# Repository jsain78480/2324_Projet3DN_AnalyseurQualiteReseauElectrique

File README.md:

# 2324_Projet3DN_AnalyseurQualiteReseauElectrique

# Consignes du projet
Il nous a été demandé de réaliser un projet de troisième année d'ingénieur en utilisant un STM32.
Le sujet de projet doit être validé avec le corps enseignant et doit être assez volumineux (Etaler sur 62h en autonomie).
Un GITHUB doit être créé et doit intégrer l'ensemble des éléments pour la création du projet (planning, cahier des charges, etc).
Il est préférable de réaliser un PCB 4 couches et de sous-traiter sa fabrication.
Les composants devront être soudé par les élèves. 

## Organisation du GITHUB

Nous avons ajouté différentes catégories dans notre GITHUB :
1) Hardware intègre tous les éléments permettant d'aboutir à la fabrication de nos PCB :       
   https://github.com/jsain78480/2324_Projet3DN_AnalyseurQualiteReseauElectrique/tree/main/Hardware 
2) Software intègre toute la programmation logiciel liée à STM32 Cube IDE :
   https://github.com/jsain78480/2324_Projet3DN_AnalyseurQualiteReseauElectrique/tree/main/Software
3) Projet intègre toute la méthodologie projet (Planning, cahier des charges) :
   https://github.com/jsain78480/2324_Projet3DN_AnalyseurQualiteReseauElectrique/tree/main/Projet

## Résumé du projet
Nous souhaitons réaliser un analyseur de réseau électrique dans le but d'évaluer la qualité d'un réseau electrique d'une entreprise.
Cette analyse permettra également à l'entreprise d'évaluer sa consommation électrique globale et de réévaluer l'offre qu'elle souscrit auprès de leur fournisseur.
Ce dispositif permet :
  - De récupérer la tension électrique du réseau monophasée ou triphasée
  - De mesurer le courant
  - De prélever la puissance du réseau
  - De prélever le spectre et en ressortir les harmoniques
  - D'afficher sur un écran les mesures instantannées
  - Gérer des alertes si le réseau comporte des problèmes

Le projet a commencé le 26 février et s'étend sur 62h. 
Vous pouvez trouver le planing du projet dans le répertoire projet.

## Le schéma du projet

## Le PCB d'acquisition

## Le PCB de traitement

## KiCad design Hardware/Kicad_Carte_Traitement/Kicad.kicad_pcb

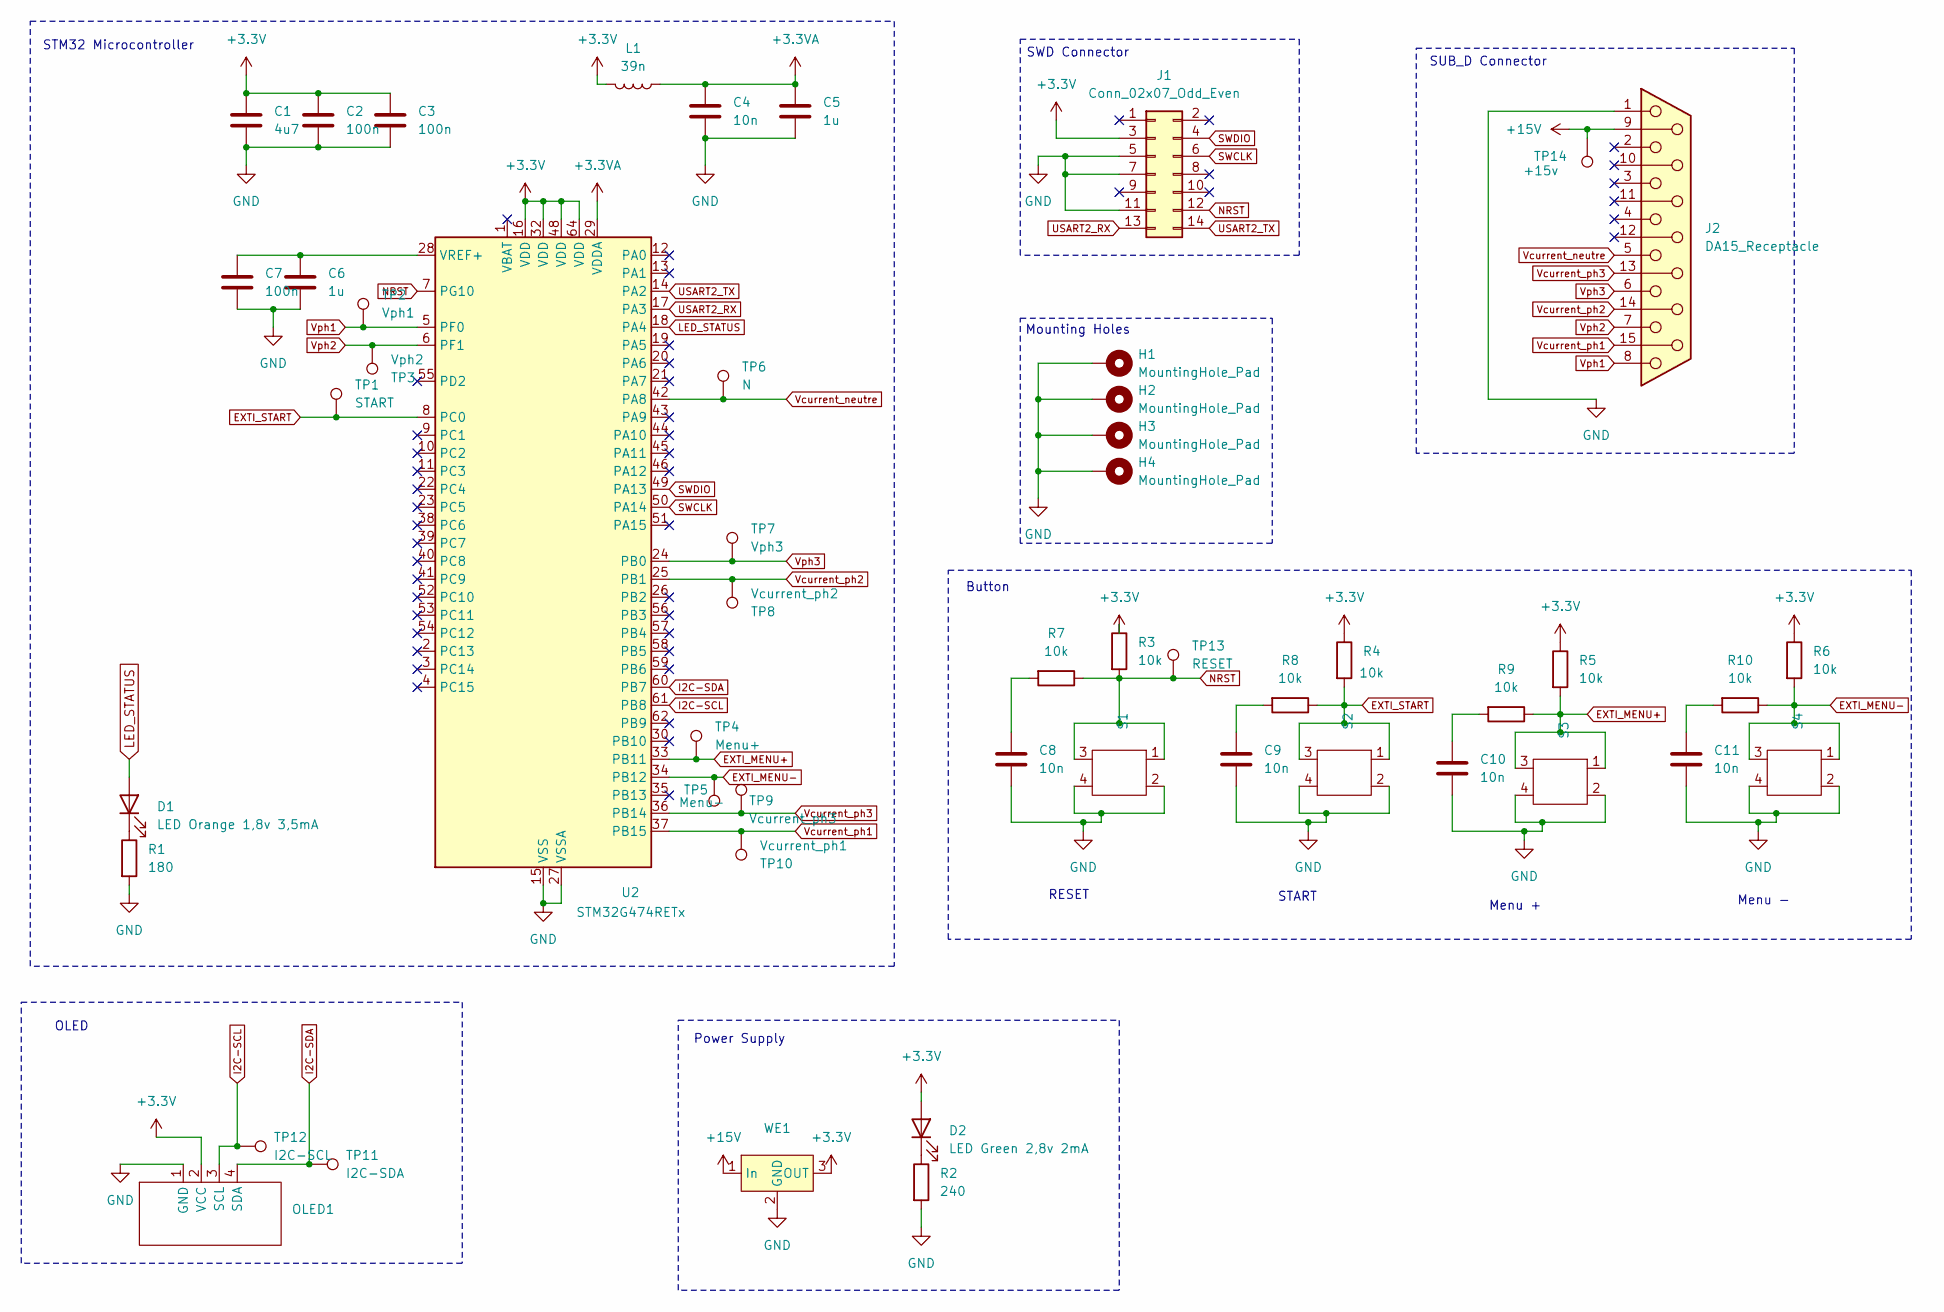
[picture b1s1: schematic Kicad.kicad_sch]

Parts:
C1: 4u7; C_0603_1608Metric_Pad1.08x0.95mm_HandSolder
C2, C3, C7: 100n; C_0603_1608Metric_Pad1.08x0.95mm_HandSolder
C4, C8, C9, C10, C11: 10n; C_0603_1608Metric_Pad1.08x0.95mm_HandSolder
C5, C6: 1u; C_0603_1608Metric_Pad1.08x0.95mm_HandSolder
D1: LED Orange 1,8v 3,5mA; LED_0603_1608Metric_Pad1.05x0.95mm_HandSolder
D2: LED Green 2,8v 2mA; LED_0603_1608Metric_Pad1.05x0.95mm_HandSolder
H1, H2, H3, H4: MountingHole_Pad; MountingHole_3.2mm_M3_Pad
J1: Conn_02x07_Odd_Even; IDC-Header_2x07_P2.54mm_Vertical_SMD
J2: DA15_Receptacle; 618015231321
L1: 39n; L_0603_1608Metric_Pad1.05x0.95mm_HandSolder
OLED1: OLED
R1: 180; R_0603_1608Metric_Pad0.98x0.95mm_HandSolder
R2: 240; R_0603_1608Metric_Pad0.98x0.95mm_HandSolder
R3, R4, R5, R6, R7, R8, R9, R10: 10k; R_0603_1608Metric_Pad0.98x0.95mm_HandSolder
S1, S2, S3, S4: Tact_switch
TP1: START; Pin_D1.2mm_L10.2mm_W2.9mm_FlatFork
TP2: Vph1; Pin_D1.2mm_L10.2mm_W2.9mm_FlatFork
TP3: Vph2; Pin_D1.2mm_L10.2mm_W2.9mm_FlatFork
TP4: Menu+; Pin_D1.2mm_L10.2mm_W2.9mm_FlatFork
TP5: Menu-; Pin_D1.2mm_L10.2mm_W2.9mm_FlatFork
TP6: N; Pin_D1.2mm_L10.2mm_W2.9mm_FlatFork
TP7: Vph3; Pin_D1.2mm_L10.2mm_W2.9mm_FlatFork
TP8: Vcurrent_ph2; Pin_D1.2mm_L10.2mm_W2.9mm_FlatFork
TP9: Vcurrent_ph3; Pin_D1.2mm_L10.2mm_W2.9mm_FlatFork
TP10: Vcurrent_ph1; Pin_D1.2mm_L10.2mm_W2.9mm_FlatFork
TP11: I2C-SDA; Pin_D1.2mm_L10.2mm_W2.9mm_FlatFork
TP12: I2C-SCL; Pin_D1.2mm_L10.2mm_W2.9mm_FlatFork
TP13: RESET; Pin_D1.2mm_L10.2mm_W2.9mm_FlatFork
TP14: +15v; Pin_D1.2mm_L10.2mm_W2.9mm_FlatFork
U2: STM32G474RETx; LQFP-64_10x10mm_P0.5mm
WE1: test

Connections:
+3.3V: C1.1, C2.1, C3.1, D2.2 (A), J1.3, L1.2, OLED1.2 (VCC), R3.1, R4.1, R5.1, R6.1, U2.16 (VDD), U2.32 (VDD), U2.48 (VDD), U2.64 (VDD), WE1.3 (OUT)
+3.3VA: C4.1, C5.1, L1.1, U2.29 (VDDA)
+15V: J2.9, TP14.1, WE1.1 (In)
EXTI_MENU+: R5.2, R9.1, S3.1, S3.3, TP4.1, U2.33 (PB11)
EXTI_MENU-: R6.2, R10.1, S4.1, S4.3, TP5.1, U2.34 (PB12)
EXTI_START: R4.2, R8.1, S2.1, S2.3, TP1.1, U2.8 (PC0)
GND: C1.2, C2.2, C3.2, C4.2, C5.2, C6.2, C7.2, C8.2, C9.2, C10.2, C11.2, H1.1, H2.1, H3.1, H4.1, J1.5, J1.7, J1.11, J2.1, OLED1.1 (GND), R1.2, R2.2, S1.2, S1.4, S2.2, S2.4, S3.2, S3.4, S4.2, S4.4, U2.15 (VSS), U2.27 (VSSA), U2.31 (VSS), U2.47 (VSS), U2.63 (VSS), WE1.2 (GND)
I2C-SCL: OLED1.3 (SCL), TP12.1, U2.61 (PB8)
I2C-SDA: OLED1.4 (SDA), TP11.1, U2.60 (PB7)
LED_STATUS: D1.2 (A), U2.18 (PA4)
NRST: J1.12, R3.2, R7.1, S1.1, S1.3, TP13.1, U2.7 (PG10)
unnamed: C8.1, R7.2
unnamed: C9.1, R8.2
unnamed: C10.1, R9.2
unnamed: C11.1, R10.2
unnamed: D1.1 (K), R1.1
unnamed: D2.1 (K), R2.1
unnamed: C6.1, C7.1, U2.28 (VREF+)
SWCLK: J1.6, U2.50 (PA14)
SWDIO: J1.4, U2.49 (PA13)
USART2_RX: J1.13, U2.17 (PA3)
USART2_TX: J1.14, U2.14 (PA2)
Vcurrent_neutre: J2.5, TP6.1, U2.42 (PA8)
Vcurrent_ph1: J2.15, TP10.1, U2.37 (PB15)
Vcurrent_ph2: J2.14, TP8.1, U2.25 (PB1)
Vcurrent_ph3: J2.13, TP9.1, U2.36 (PB14)
Vph1: J2.8, TP2.1, U2.5 (PF0)
Vph2: J2.7, TP3.1, U2.6 (PF1)
Vph3: J2.6, TP7.1, U2.24 (PB0)

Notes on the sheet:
STM32 Microcontroller
Power Supply
SUB_D Connector
Menu -
Button
SWD Connector
OLED
START
RESET
Menu +
Mounting Holes

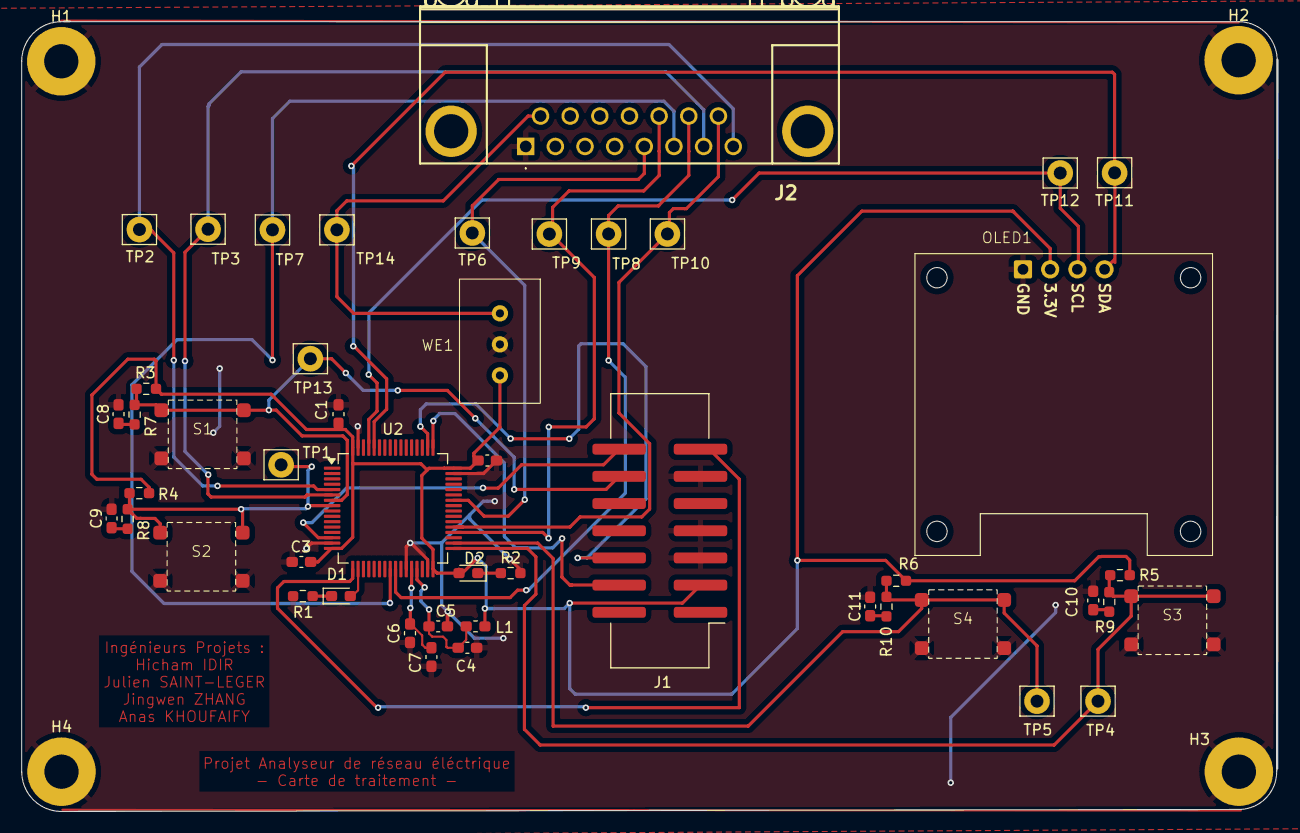
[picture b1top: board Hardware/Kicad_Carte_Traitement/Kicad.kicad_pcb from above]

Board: 2 copper layers, 117.3 x 73.8 mm, 51 parts (0 on the bottom side), 29 nets.

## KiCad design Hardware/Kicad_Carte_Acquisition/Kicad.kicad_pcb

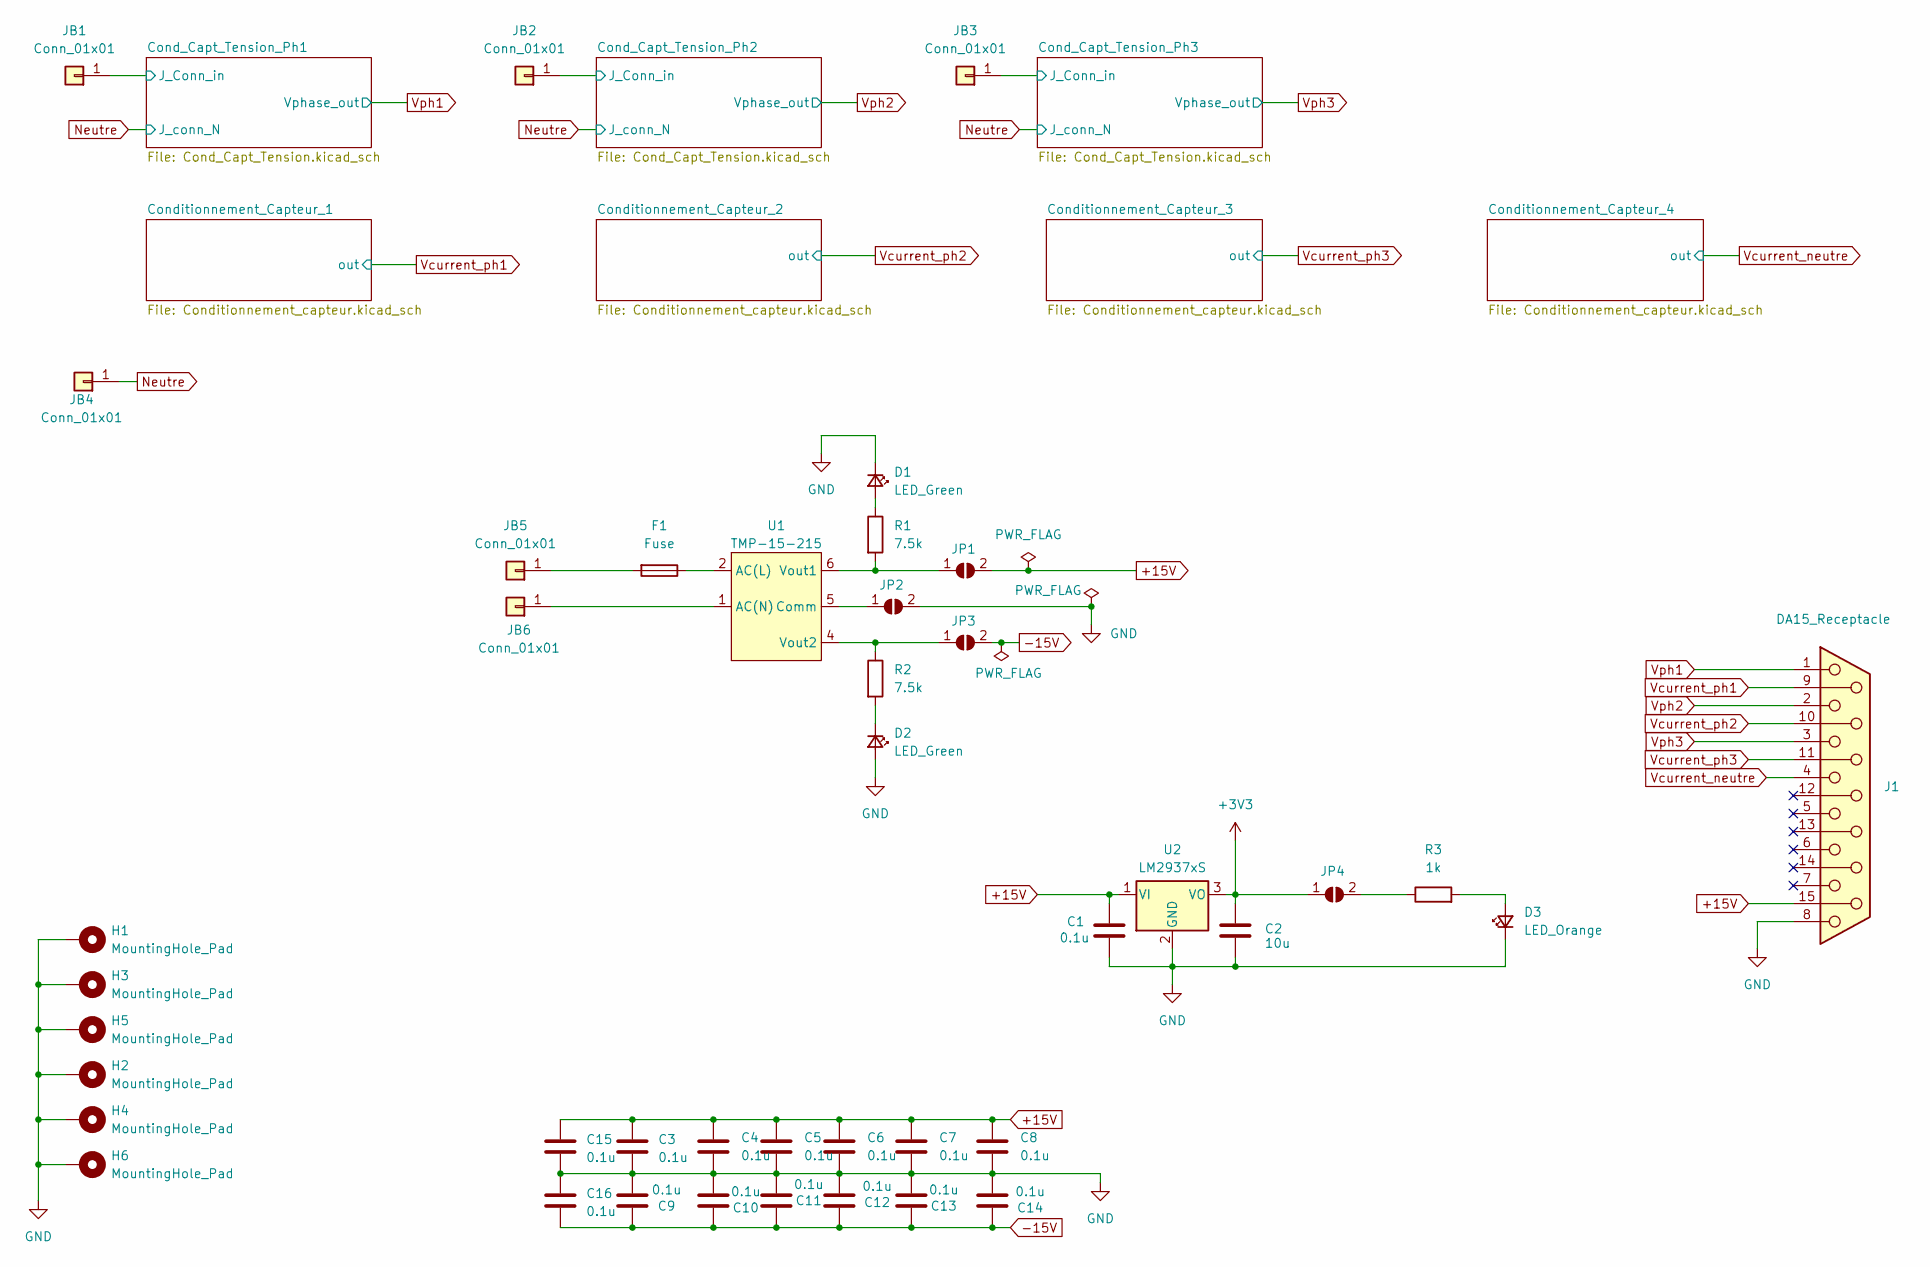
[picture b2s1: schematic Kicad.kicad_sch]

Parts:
C1, C3, C4, C5, C6, C7, C8, C9, C10, C11, C12, C13, C14, C15, C16: 0.1u; C_0603_1608Metric_Pad1.08x0.95mm_HandSolder
C2: 10u; C_0603_1608Metric_Pad1.08x0.95mm_HandSolder
D1, D2: LED_Green; LED_0603_1608Metric_Pad1.05x0.95mm_HandSolder
D3: LED_Orange; LED_0603_1608Metric_Pad1.05x0.95mm_HandSolder
F1: Fuse; Porte_Fusible_PC1E
H1, H2, H3, H4, H5, H6: MountingHole_Pad; MountingHole_3.2mm_M3_Pad
J1: DA15_Receptacle; 618015231321
JB1, JB2, JB3, JB4, JB5, JB6: Conn_01x01; Banana_Cliff_FCR7350B_S16N-PC_Horizontal
JP1, JP2, JP3, JP4: SolderJumper_2_Open; SolderJumper-2_P1.3mm_Open_TrianglePad1.0x1.5mm
R1, R2: 7.5k; R_0603_1608Metric_Pad0.98x0.95mm_HandSolder
R3: 1k; R_0603_1608Metric_Pad0.98x0.95mm_HandSolder
U1: TMP-15-215; TMP-15-215E
U2: LM2937xS; TO-263-3_TabPin2

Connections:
+3V3: C2.1, JP4.1 (A), U2.3 (VO); also elsewhere on the board
+15V: C1.1, C3.1, C4.1, C5.1, C6.1, C7.1, C8.1, C15.1, J1.15, JP1.2 (B), U2.1 (VI); also elsewhere on the board
-15V: C9.1, C10.1, C11.1, C12.1, C13.1, C14.1, C16.2, JP3.2 (B); also elsewhere on the board
/Cond_Capt_Tension_Ph1/J_Conn_in: JB1.1; also elsewhere on the board
/Cond_Capt_Tension_Ph2/J_Conn_in: JB2.1; also elsewhere on the board
/Cond_Capt_Tension_Ph3/J_Conn_in: JB3.1; also elsewhere on the board
GND: C1.2, C2.2, C3.2, C4.2, C5.2, C6.2, C7.2, C8.2, C9.2, C10.2, C11.2, C12.2, C13.2, C14.2, C15.2, C16.1, D1.1 (K), D2.2 (A), D3.1 (K), H1.1, H2.1, H3.1, H4.1, H5.1, H6.1, J1.8, JP2.2 (B), U2.2 (GND); also elsewhere on the board
unnamed: D1.2 (A), R1.1
unnamed: D2.1 (K), R2.2
unnamed: D3.2 (A), R3.2
unnamed: F1.2, JB5.1
unnamed: JB6.1, U1.1 (AC(N))
unnamed: JP1.1 (A), R1.2, U1.6 (Vout1)
unnamed: JP2.1 (A), U1.5 (Comm)
unnamed: JP3.1 (A), R2.1, U1.4 (Vout2)
unnamed: JP4.2 (B), R3.1
unnamed: F1.1, U1.2 (AC(L))
Neutre: JB4.1; also elsewhere on the board
Vcurrent_neutre: J1.4; also elsewhere on the board
Vcurrent_ph1: J1.9; also elsewhere on the board
Vcurrent_ph2: J1.10; also elsewhere on the board
Vcurrent_ph3: J1.11 (P111); also elsewhere on the board
Vph1: J1.1; also elsewhere on the board
Vph2: J1.2; also elsewhere on the board
Vph3: J1.3; also elsewhere on the board

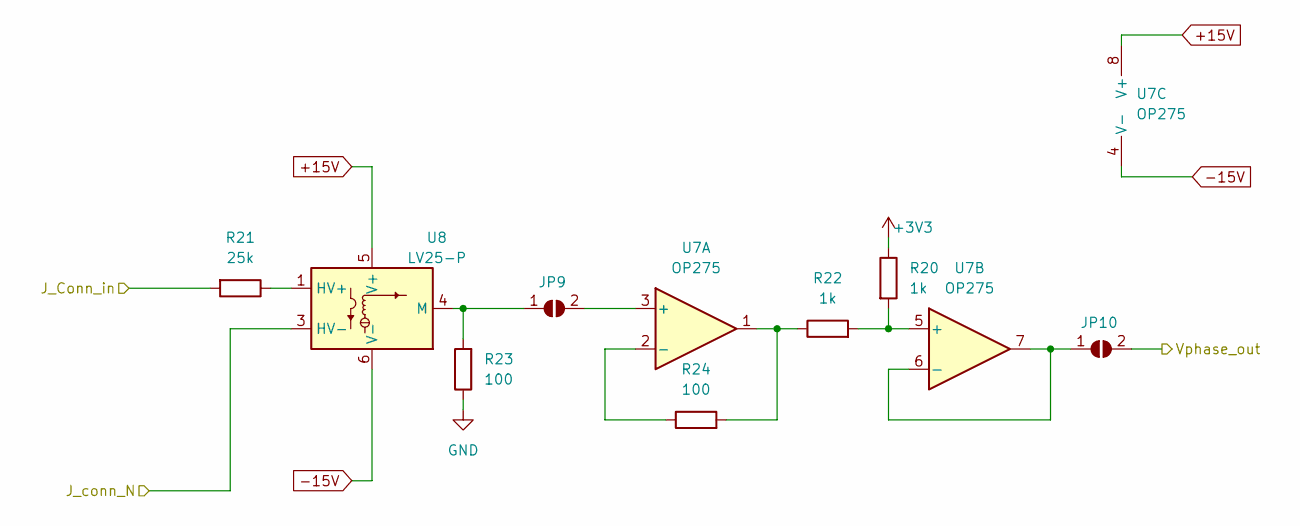
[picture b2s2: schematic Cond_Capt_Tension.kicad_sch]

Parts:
JP9, JP10: SolderJumper_2_Open; SolderJumper-2_P1.3mm_Open_TrianglePad1.0x1.5mm
R20, R22: 1k; R_0603_1608Metric_Pad0.98x0.95mm_HandSolder
R21: 25k; R_4527_M11470E
R23, R24: 100; R_0603_1608Metric_Pad0.98x0.95mm_HandSolder
U7: OP275; SOIC-8_3.9x4.9mm_P1.27mm
U8: LV25-P; LEM_LV25-P

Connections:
+3V3: R20.1; also elsewhere on the board
+15V: U7.8 (V+), U8.5 (V+); also elsewhere on the board
-15V: U7.4 (V-), U8.6 (V-); also elsewhere on the board
/Cond_Capt_Tension_Ph1/J_Conn_in: R21.2; also elsewhere on the board
GND: R23.1; also elsewhere on the board
unnamed: JP9.1 (A), R23.2, U8.4 (M)
unnamed: JP9.2 (B), U7.3 (+)
unnamed: JP10.1 (A), U7.6 (-), U7.7
unnamed: R22.1, R24.2, U7.1
unnamed: R24.1, U7.2 (-)
unnamed: R20.2, R22.2, U7.5 (+)
unnamed: R21.1, U8.1 (HV+)
Neutre: U8.3 (HV-); also elsewhere on the board
Vph1: JP10.2 (B); also elsewhere on the board

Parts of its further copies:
JP11, JP12, JP13, JP14: SolderJumper_2_Open; SolderJumper-2_P1.3mm_Open_TrianglePad1.0x1.5mm
R25, R27, R30, R32: 1k; R_0603_1608Metric_Pad0.98x0.95mm_HandSolder
R26, R31: 25k; R_4527_M11470E
R28, R29, R33, R34: 100; R_0603_1608Metric_Pad0.98x0.95mm_HandSolder
U9, U11: OP275; SOIC-8_3.9x4.9mm_P1.27mm
U10, U12: LV25-P; LEM_LV25-P

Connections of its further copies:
+3V3: R25.1, R30.1; also elsewhere on the board
+15V: U9.8 (V+), U10.5 (V+), U11.8 (V+), U12.5 (V+); also elsewhere on the board
-15V: U9.4 (V-), U10.6 (V-), U11.4 (V-), U12.6 (V-); also elsewhere on the board
/Cond_Capt_Tension_Ph2/J_Conn_in: R26.2; also elsewhere on the board
/Cond_Capt_Tension_Ph3/J_Conn_in: R31.2; also elsewhere on the board
GND: R28.1, R33.1; also elsewhere on the board
unnamed: JP11.1 (A), R28.2, U10.4 (M)
unnamed: JP11.2 (B), U9.3 (+)
unnamed: JP12.1 (A), U9.6 (-), U9.7
unnamed: JP13.1 (A), R33.2, U12.4 (M)
unnamed: JP13.2 (B), U11.3 (+)
unnamed: JP14.1 (A), U11.6 (-), U11.7
unnamed: R27.1, R29.2, U9.1
unnamed: R32.1, R34.2, U11.1
unnamed: R29.1, U9.2 (-)
unnamed: R25.2, R27.2, U9.5 (+)
unnamed: R26.1, U10.1 (HV+)
unnamed: R34.1, U11.2 (-)
unnamed: R30.2, R32.2, U11.5 (+)
unnamed: R31.1, U12.1 (HV+)
Neutre: U10.3 (HV-), U12.3 (HV-); also elsewhere on the board
Vph2: JP12.2 (B); also elsewhere on the board
Vph3: JP14.2 (B); also elsewhere on the board

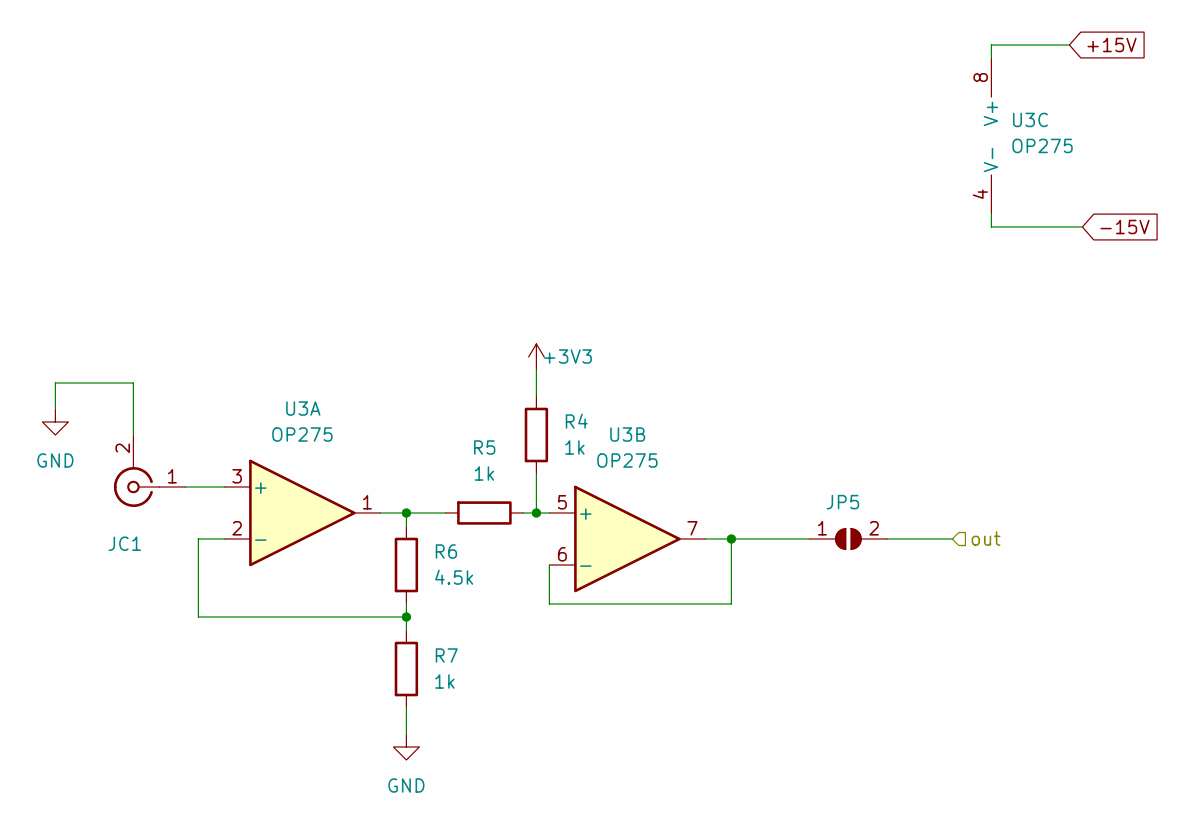
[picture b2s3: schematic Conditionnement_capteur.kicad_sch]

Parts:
JC1: Conn_Coaxial; Conn_CoaxE
JP5: SolderJumper_2_Open; SolderJumper-2_P1.3mm_Open_TrianglePad1.0x1.5mm
R4, R5, R7: 1k; R_0603_1608Metric_Pad0.98x0.95mm_HandSolder
R6: 4.5k; R_0603_1608Metric_Pad0.98x0.95mm_HandSolder
U3: OP275; SOIC-8_3.9x4.9mm_P1.27mm

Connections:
+3V3: R4.1; also elsewhere on the board
+15V: U3.8 (V+); also elsewhere on the board
-15V: U3.4 (V-); also elsewhere on the board
GND: JC1.2 (Ext), R7.2; also elsewhere on the board
unnamed: JC1.1 (In), U3.3 (+)
unnamed: JP5.1 (A), U3.6 (-), U3.7
unnamed: R5.2, R6.1, U3.1
unnamed: R6.2, R7.1, U3.2 (-)
unnamed: R4.2, R5.1, U3.5 (+)
Vcurrent_ph1: JP5.2 (B); also elsewhere on the board

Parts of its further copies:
JC2, JC3, JC4: Conn_Coaxial; Conn_CoaxE
JP6, JP7, JP8: SolderJumper_2_Open; SolderJumper-2_P1.3mm_Open_TrianglePad1.0x1.5mm
R8, R9, R11, R12, R13, R15, R16, R17, R19: 1k; R_0603_1608Metric_Pad0.98x0.95mm_HandSolder
R10, R14, R18: 4.5k; R_0603_1608Metric_Pad0.98x0.95mm_HandSolder
U4, U5, U6: OP275; SOIC-8_3.9x4.9mm_P1.27mm

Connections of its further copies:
+3V3: R8.1, R12.1, R16.1; also elsewhere on the board
+15V: U4.8 (V+), U5.8 (V+), U6.8 (V+); also elsewhere on the board
-15V: U4.4 (V-), U5.4 (V-), U6.4 (V-); also elsewhere on the board
GND: JC2.2 (Ext), JC3.2 (Ext), JC4.2 (Ext), R11.2, R15.2, R19.2; also elsewhere on the board
unnamed: JC2.1 (In), U4.3 (+)
unnamed: JC3.1 (In), U5.3 (+)
unnamed: JC4.1 (In), U6.3 (+)
unnamed: JP6.1 (A), U4.6 (-), U4.7
unnamed: JP7.1 (A), U5.6 (-), U5.7
unnamed: JP8.1 (A), U6.6 (-), U6.7
unnamed: R9.2, R10.1, U4.1
unnamed: R13.2, R14.1, U5.1
unnamed: R17.2, R18.1, U6.1
unnamed: R10.2, R11.1, U4.2 (-)
unnamed: R8.2, R9.1, U4.5 (+)
unnamed: R14.2, R15.1, U5.2 (-)
unnamed: R12.2, R13.1, U5.5 (+)
unnamed: R18.2, R19.1, U6.2 (-)
unnamed: R16.2, R17.1, U6.5 (+)
Vcurrent_neutre: JP8.2 (B); also elsewhere on the board
Vcurrent_ph2: JP6.2 (B); also elsewhere on the board
Vcurrent_ph3: JP7.2 (B); also elsewhere on the board

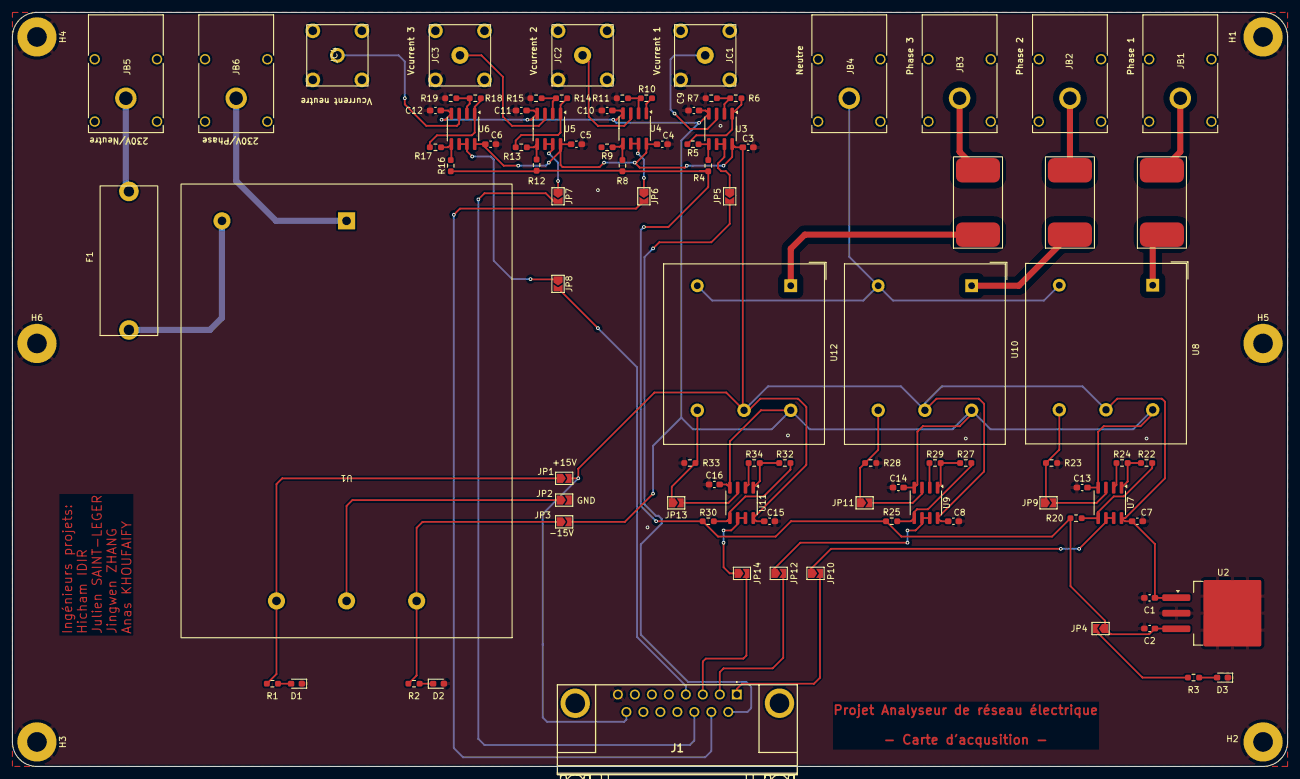
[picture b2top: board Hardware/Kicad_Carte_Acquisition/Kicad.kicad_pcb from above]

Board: 2 copper layers, 208.0 x 123.0 mm, 97 parts (0 on the bottom side), 66 nets.

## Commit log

2024-02-26 Ajout KICAD
2024-02-29 modifs
2024-03-15 capteur de la tension
2024-03-22 modif
2024-03-22 Fin TP 22 mars
2024-03-28 MAJ Prof
2024-03-28 Hicham_modif
2024-04-04 Récupération tension avec ADC - sans tableau
2024-04-04 Miseajour1
2024-04-05 miseajour
2024-04-22 Rename hardware.txt to hardware.md
2024-04-22 Rename journal-de-bord.txt to journal-de-bord.md
2024-05-05 maj ju
2024-06-19 push
